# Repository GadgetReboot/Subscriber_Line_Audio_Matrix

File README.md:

# Subscriber_Line_Audio_Matrix
8x8 audio matrix with phone jacks for use in a phone line simulator project

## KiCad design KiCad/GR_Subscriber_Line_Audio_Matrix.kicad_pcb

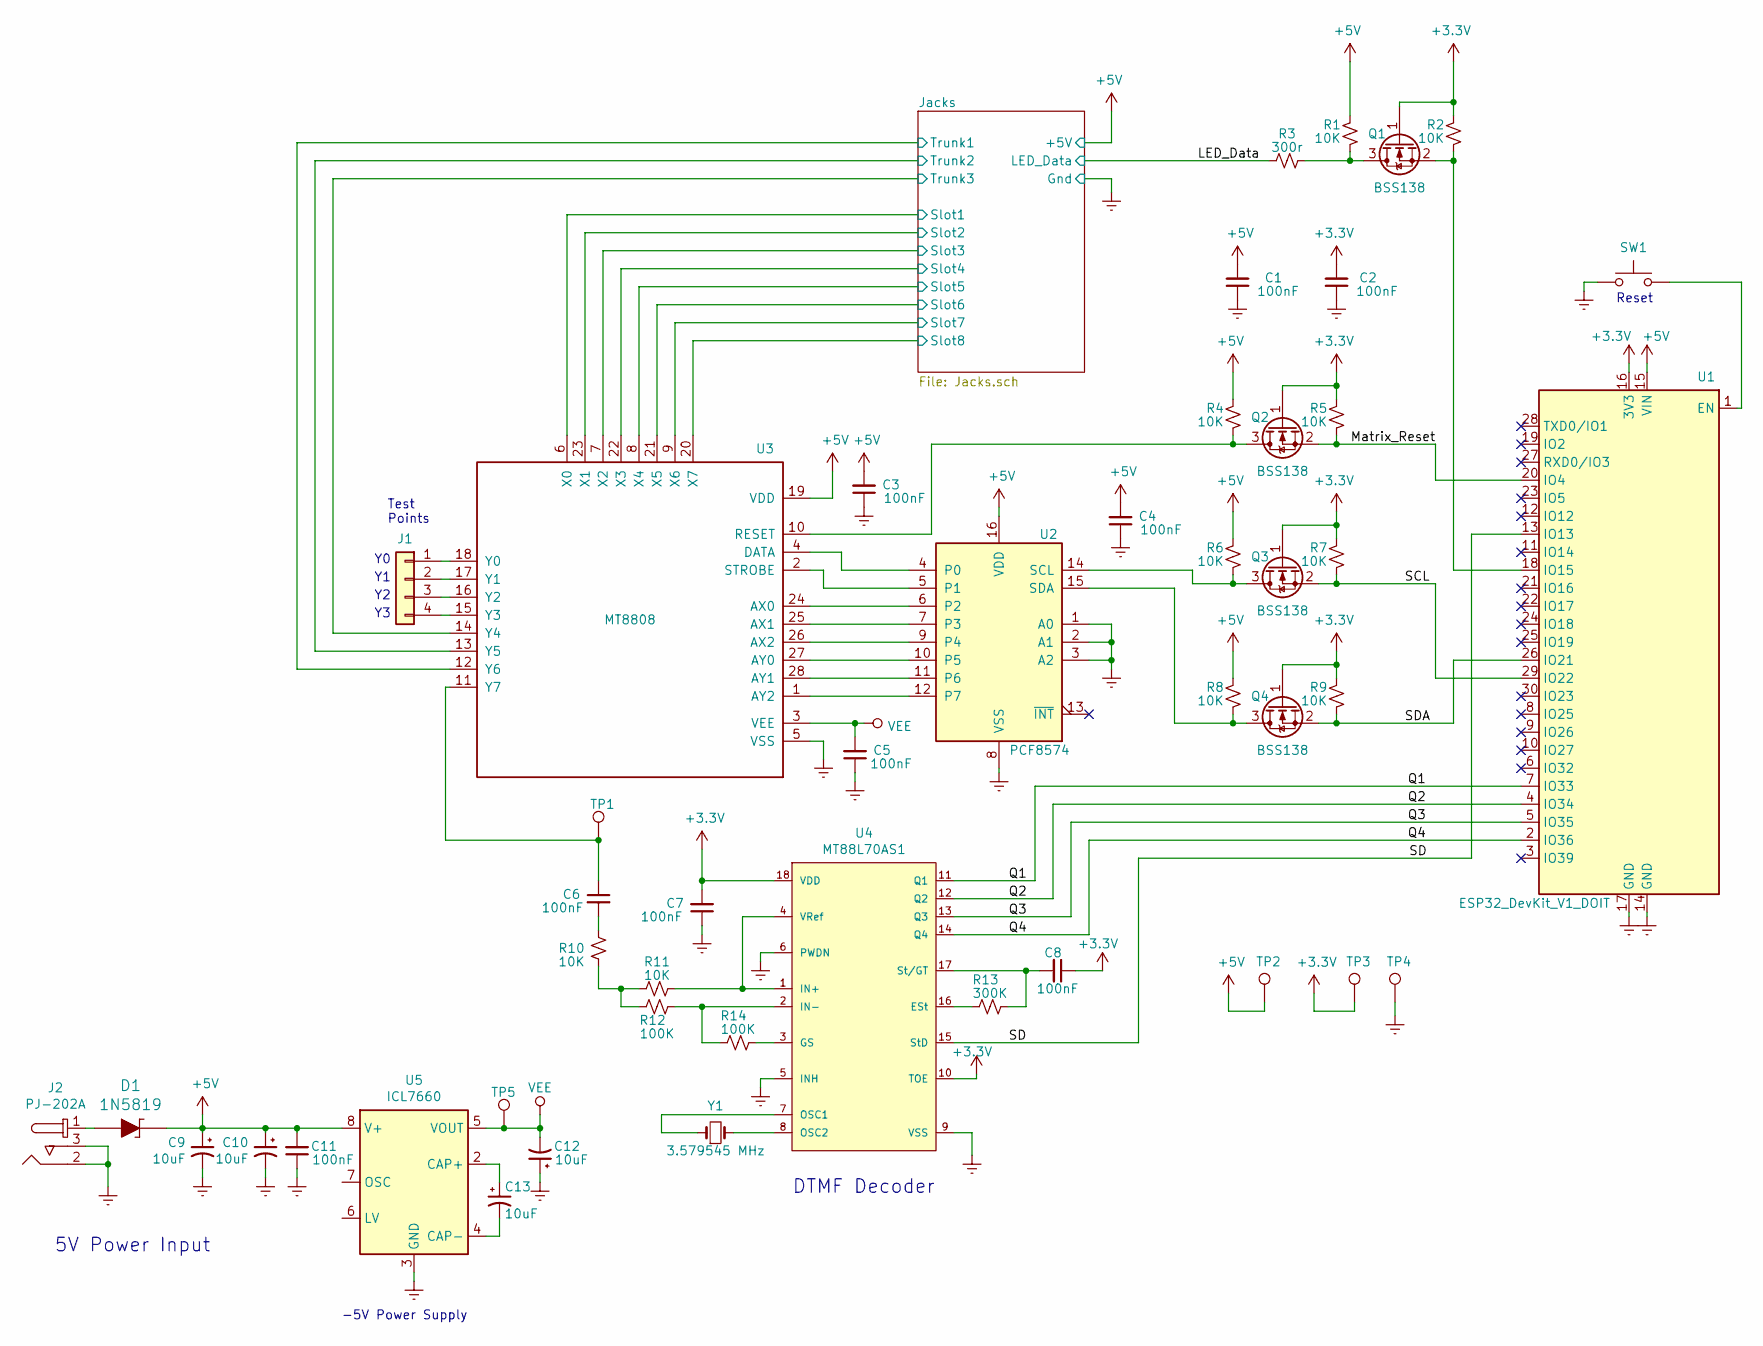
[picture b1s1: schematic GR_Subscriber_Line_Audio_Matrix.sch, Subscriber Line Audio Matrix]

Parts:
C1, C2, C3, C4, C5, C6, C7, C8, C11: 100nF; C_0805_2012Metric_Pad1.15x1.40mm_HandSolder
C9, C10, C12, C13: 10uF; CP_Elec_4x4.5
D1: 1N5819; SOD-123
J1: Conn_01x04; PinHeader_1x04_P2.54mm_Vertical
J2: PJ-202A; Barrel_Jack_5.5mmODx2.1mmID_PJ-202A; MPN PJ-202A; Digi-Key_PN CP-202A-ND
Q1, Q2, Q3, Q4: BSS138; SOT-23
R1, R2, R4, R5, R6, R7, R8, R9, R10, R11: 10K; R_0805_2012Metric_Pad1.15x1.40mm_HandSolder
R3: 300r; R_0805_2012Metric_Pad1.15x1.40mm_HandSolder
R12, R14: 100K; R_0805_2012Metric_Pad1.15x1.40mm_HandSolder
R13: 300K; R_0805_2012Metric_Pad1.15x1.40mm_HandSolder
SW1: SW_Push; SW_SPST_60x35
TP1, TP2, TP3, TP4, TP5: TestPoint; TestPoint_Loop_D3.50mm_Drill0.9mm_Beaded
U1: ESP32_DevKit_V1_DOIT; esp32_devkit_v1_doit
U2: PCF8574; SOIC-16W_7.5x10.3mm_P1.27mm
U3: MT8808; DIP-28_W15.24mm_Socket_LongPads
U4: MT88L70AS1; SOIC-18W_7.5x11.6mm_P1.27mm
U5: ICL7660; SOIC-8_3.9x4.9mm_P1.27mm
Y1: 3.579545 MHz; Crystal_SMD_HC49-SD_HandSoldering

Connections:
+3V3: C2.2, C7.2, C8.1, Q1.1 (G), Q2.1 (G), Q3.1 (G), Q4.1 (G), R2.1, R5.1, R7.1, R9.1, TP3.1, U1.16 (3V3), U4.10 (TOE), U4.18 (VDD)
+5V: C1.2, C3.2, C4.2, C9.1, C10.1, C11.2, D1.K, R1.1, R4.1, R6.1, R8.1, TP2.1, U1.15 (VIN), U2.16 (VDD), U3.19 (VDD), U5.8 (V+); also elsewhere on the board
/Jacks/Slot1: U3.6 (X0); also elsewhere on the board
/Jacks/Slot2: U3.23 (X1); also elsewhere on the board
/Jacks/Slot3: U3.7 (X2); also elsewhere on the board
/Jacks/Slot4: U3.22 (X3); also elsewhere on the board
/Jacks/Slot5: U3.8 (X4); also elsewhere on the board
/Jacks/Slot6: U3.21 (X5); also elsewhere on the board
/Jacks/Slot7: U3.9 (X6); also elsewhere on the board
/Jacks/Slot8: U3.20 (X7); also elsewhere on the board
/Jacks/Trunk1: U3.12 (Y6); also elsewhere on the board
/Jacks/Trunk2: U3.13 (Y5); also elsewhere on the board
/Jacks/Trunk3: U3.14 (Y4); also elsewhere on the board
/LED_Data: R3.1; also elsewhere on the board
/Matrix_Reset: Q2.2 (S), R5.2, U1.20 (IO4)
/Q1: U1.7 (IO33), U4.11 (Q1)
/Q2: U1.4 (IO34), U4.12 (Q2)
/Q3: U1.5 (IO35), U4.13 (Q3)
/Q4: U1.2 (IO36), U4.14 (Q4)
/SCL: Q3.2 (S), R7.2, U1.29 (IO22)
/SD: U1.13 (IO13), U4.15 (StD)
/SDA: Q4.2 (S), R9.2, U1.26 (IO21)
GNDREF: C1.1, C2.1, C3.1, C4.1, C5.1, C7.1, C9.2, C10.2, C11.1, C12.1, J2.2, J2.3, SW1.1, TP4.1, U1.14 (GND), U1.17 (GND), U2.1 (A0), U2.2 (A1), U2.3 (A2), U2.8 (VSS), U3.5 (VSS), U4.5 (INH), U4.6 (PWDN), U4.9 (VSS), U5.3 (GND); also elsewhere on the board
unnamed: C6.1, TP1.1, U3.11 (Y7)
unnamed: C6.2, R10.1
unnamed: C8.2, R13.1, U4.17 (St/GT)
unnamed: C13.1, U5.2 (CAP+)
unnamed: C13.2, U5.4 (CAP-)
unnamed: D1.A, J2.1
unnamed: J1.1, U3.18 (Y0)
unnamed: J1.2, U3.17 (Y1)
unnamed: J1.3, U3.16 (Y2)
unnamed: J1.4, U3.15 (Y3)
unnamed: Q1.2 (S), R2.2, U1.18 (IO15)
unnamed: Q1.3 (D), R1.2, R3.2
unnamed: Q2.3 (D), R4.2, U3.10 (RESET)
unnamed: Q3.3 (D), R6.2, U2.14 (SCL)
unnamed: Q4.3 (D), R8.2, U2.15 (SDA)
unnamed: R10.2, R11.1, R12.2
unnamed: R11.2, U4.1 (IN+), U4.4 (VRef)
unnamed: R12.1, R14.2, U4.2 (IN-)
unnamed: R13.2, U4.16 (ESt)
unnamed: R14.1, U4.3 (GS)
unnamed: SW1.2, U1.1 (EN)
unnamed: U2.4 (P0), U3.4 (DATA)
unnamed: U2.5 (P1), U3.2 (STROBE)
unnamed: U2.6 (P2), U3.24 (AX0)
unnamed: U2.7 (P3), U3.25 (AX1)
unnamed: U2.9 (P4), U3.26 (AX2)
unnamed: U2.10 (P5), U3.27 (AY0)
unnamed: U2.11 (P6), U3.28 (AY1)
unnamed: U2.12 (P7), U3.1 (AY2)
unnamed: U4.7 (OSC1), Y1.1
unnamed: U4.8 (OSC2), Y1.2
VEE: C5.2, C12.2, TP5.1, U3.3 (VEE), U5.5 (VOUT)

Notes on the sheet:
DTMF Decoder
Test Points
5V Power Input
Reset
-5V Power Supply

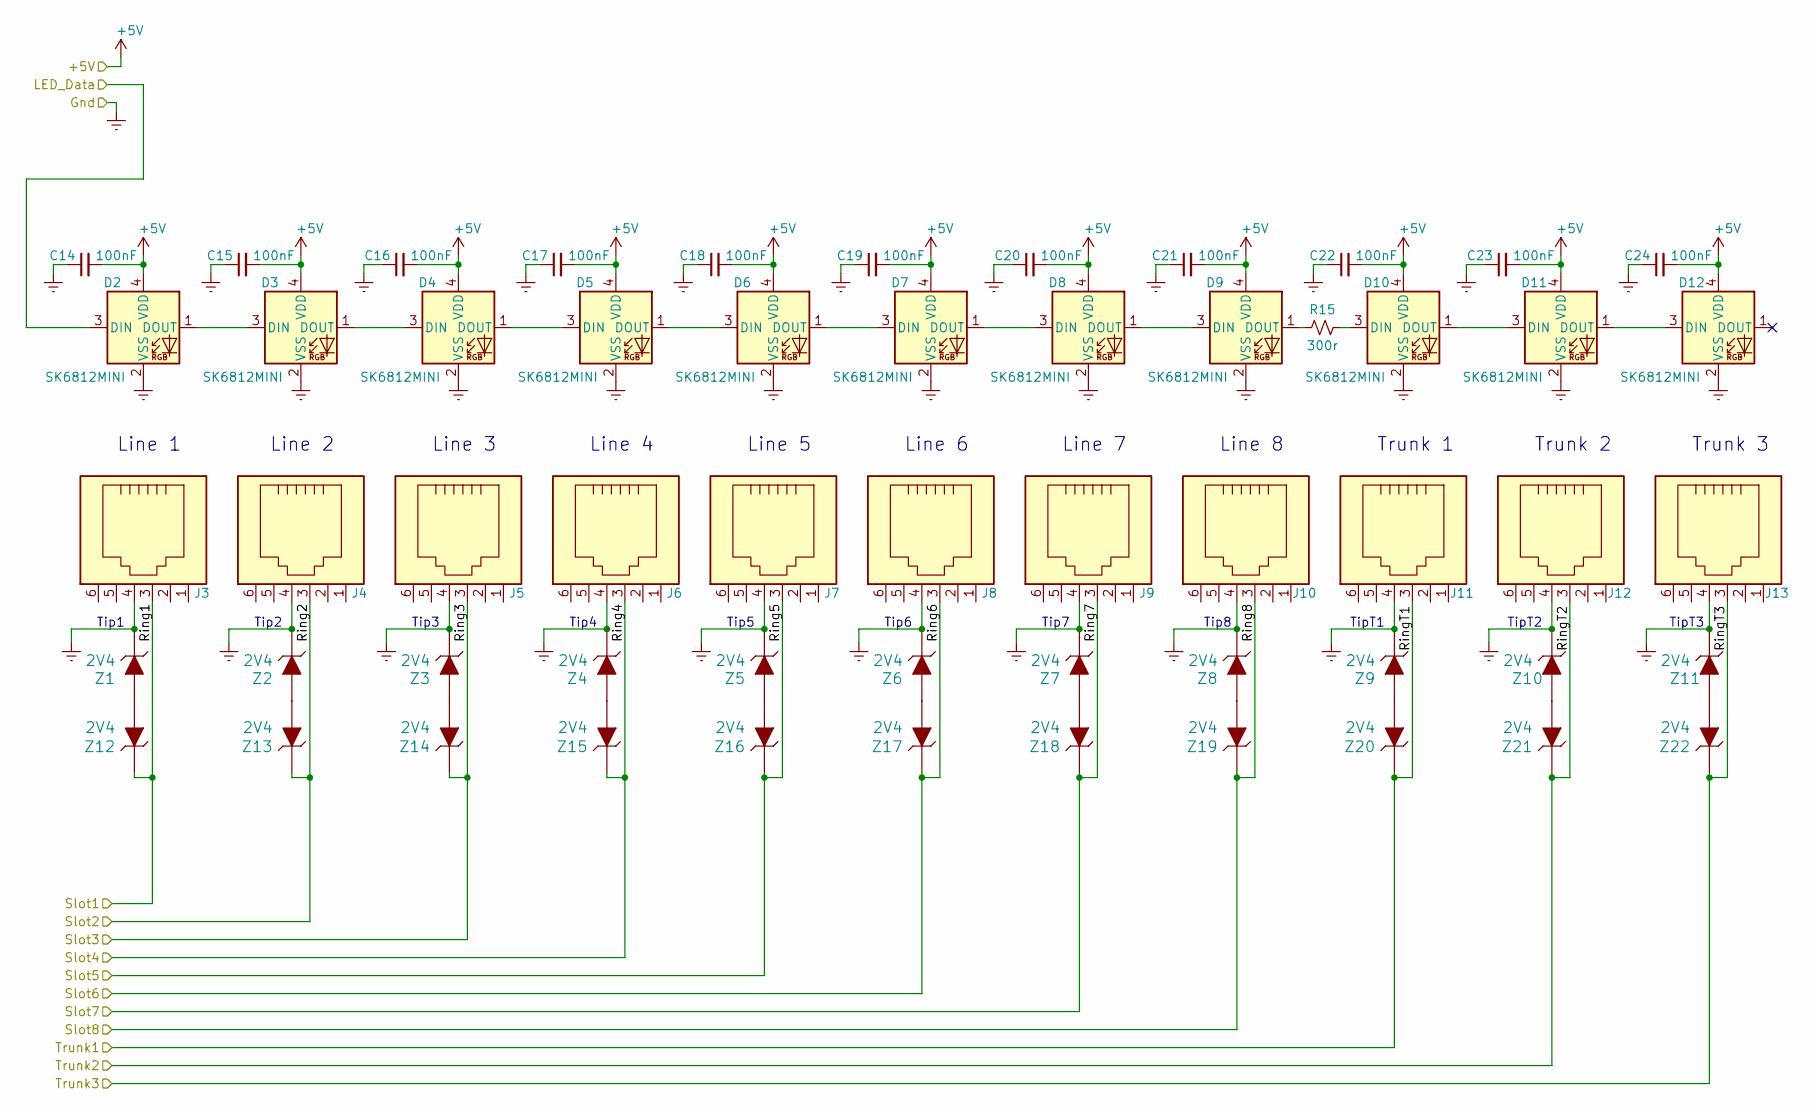
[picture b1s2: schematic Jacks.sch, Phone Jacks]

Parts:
C14, C15, C16, C17, C18, C19, C20, C21, C22, C23, C24: 100nF; C_0805_2012Metric_Pad1.15x1.40mm_HandSolder
D2, D3, D4, D5, D6, D7, D8, D9, D10, D11, D12: SK6812MINI; LED_SK6812MINI_4_3.5x3.5mm_P1.75mm
J3, J4, J5, J6, J7, J8, J9, J10, J11, J12, J13: RJ12; RJ_6p6c
R15: 300r; R_0805_2012Metric_Pad1.15x1.40mm_HandSolder
Z1, Z2, Z3, Z4, Z5, Z6, Z7, Z8, Z9, Z10, Z11, Z12, Z13, Z14, Z15, Z16, Z17, Z18, Z19, Z20, Z21, Z22: 2V4; SOD-123; MPN ZMM3.3; Digi-Key_PN Diotec Semiconductor

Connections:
+5V: C14.2, C15.2, C16.2, C17.2, C18.2, C19.2, C20.2, C21.2, C22.2, C23.2, C24.2, D2.4 (VDD), D3.4 (VDD), D4.4 (VDD), D5.4 (VDD), D6.4 (VDD), D7.4 (VDD), D8.4 (VDD), D9.4 (VDD), D10.4 (VDD), D11.4 (VDD), D12.4 (VDD); also elsewhere on the board
/Jacks/Slot1: J3.3, Z12.K; also elsewhere on the board
/Jacks/Slot2: J4.3, Z13.K; also elsewhere on the board
/Jacks/Slot3: J5.3, Z14.K; also elsewhere on the board
/Jacks/Slot4: J6.3, Z15.K; also elsewhere on the board
/Jacks/Slot5: J7.3, Z16.K; also elsewhere on the board
/Jacks/Slot6: J8.3, Z17.K; also elsewhere on the board
/Jacks/Slot7: J9.3, Z18.K; also elsewhere on the board
/Jacks/Slot8: J10.3, Z19.K; also elsewhere on the board
/Jacks/Trunk1: J11.3, Z20.K; also elsewhere on the board
/Jacks/Trunk2: J12.3, Z21.K; also elsewhere on the board
/Jacks/Trunk3: J13.3, Z22.K; also elsewhere on the board
/LED_Data: D2.3 (DIN); also elsewhere on the board
GNDREF: C14.1, C15.1, C16.1, C17.1, C18.1, C19.1, C20.1, C21.1, C22.1, C23.1, C24.1, D2.2 (VSS), D3.2 (VSS), D4.2 (VSS), D5.2 (VSS), D6.2 (VSS), D7.2 (VSS), D8.2 (VSS), D9.2 (VSS), D10.2 (VSS), D11.2 (VSS), D12.2 (VSS), J3.4, J4.4, J5.4, J6.4, J7.4, J8.4, J9.4, J10.4, J11.4, J12.4, J13.4, Z1.K, Z2.K, Z3.K, Z4.K, Z5.K, Z6.K, Z7.K, Z8.K, Z9.K, Z10.K, Z11.K; also elsewhere on the board
unnamed: D2.1 (DOUT), D3.3 (DIN)
unnamed: D3.1 (DOUT), D4.3 (DIN)
unnamed: D4.1 (DOUT), D5.3 (DIN)
unnamed: D5.1 (DOUT), D6.3 (DIN)
unnamed: D6.1 (DOUT), D7.3 (DIN)
unnamed: D7.1 (DOUT), D8.3 (DIN)
unnamed: D8.1 (DOUT), D9.3 (DIN)
unnamed: D9.1 (DOUT), R15.1
unnamed: D10.1 (DOUT), D11.3 (DIN)
unnamed: D10.3 (DIN), R15.2
unnamed: D11.1 (DOUT), D12.3 (DIN)
unnamed: Z1.A, Z12.A
unnamed: Z10.A, Z21.A
unnamed: Z11.A, Z22.A
unnamed: Z2.A, Z13.A
unnamed: Z3.A, Z14.A
unnamed: Z4.A, Z15.A
unnamed: Z5.A, Z16.A
unnamed: Z6.A, Z17.A
unnamed: Z7.A, Z18.A
unnamed: Z8.A, Z19.A
unnamed: Z9.A, Z20.A

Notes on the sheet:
Line 1
Line 2
Line 3
Line 4
Line 5
Line 6
Line 7
Line 8
Tip8
Tip7
Tip6
Tip5
Tip4
Tip3
Tip2
Tip1
Trunk 1
Trunk 2
Trunk 3
TipT3
TipT2
TipT1

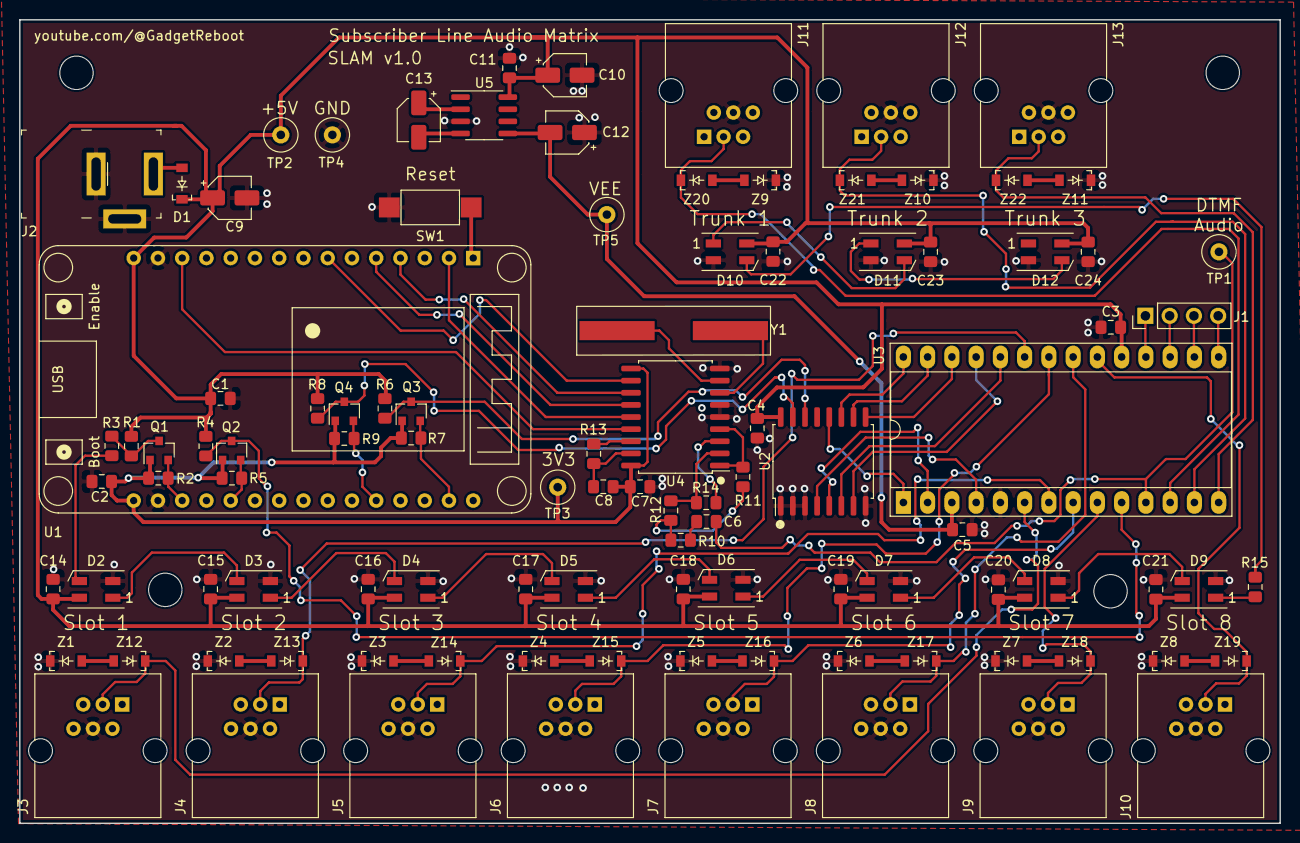
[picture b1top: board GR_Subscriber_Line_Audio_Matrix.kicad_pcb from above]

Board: 2 copper layers, 132.0 x 84.2 mm, 102 parts (0 on the bottom side), 77 nets.
